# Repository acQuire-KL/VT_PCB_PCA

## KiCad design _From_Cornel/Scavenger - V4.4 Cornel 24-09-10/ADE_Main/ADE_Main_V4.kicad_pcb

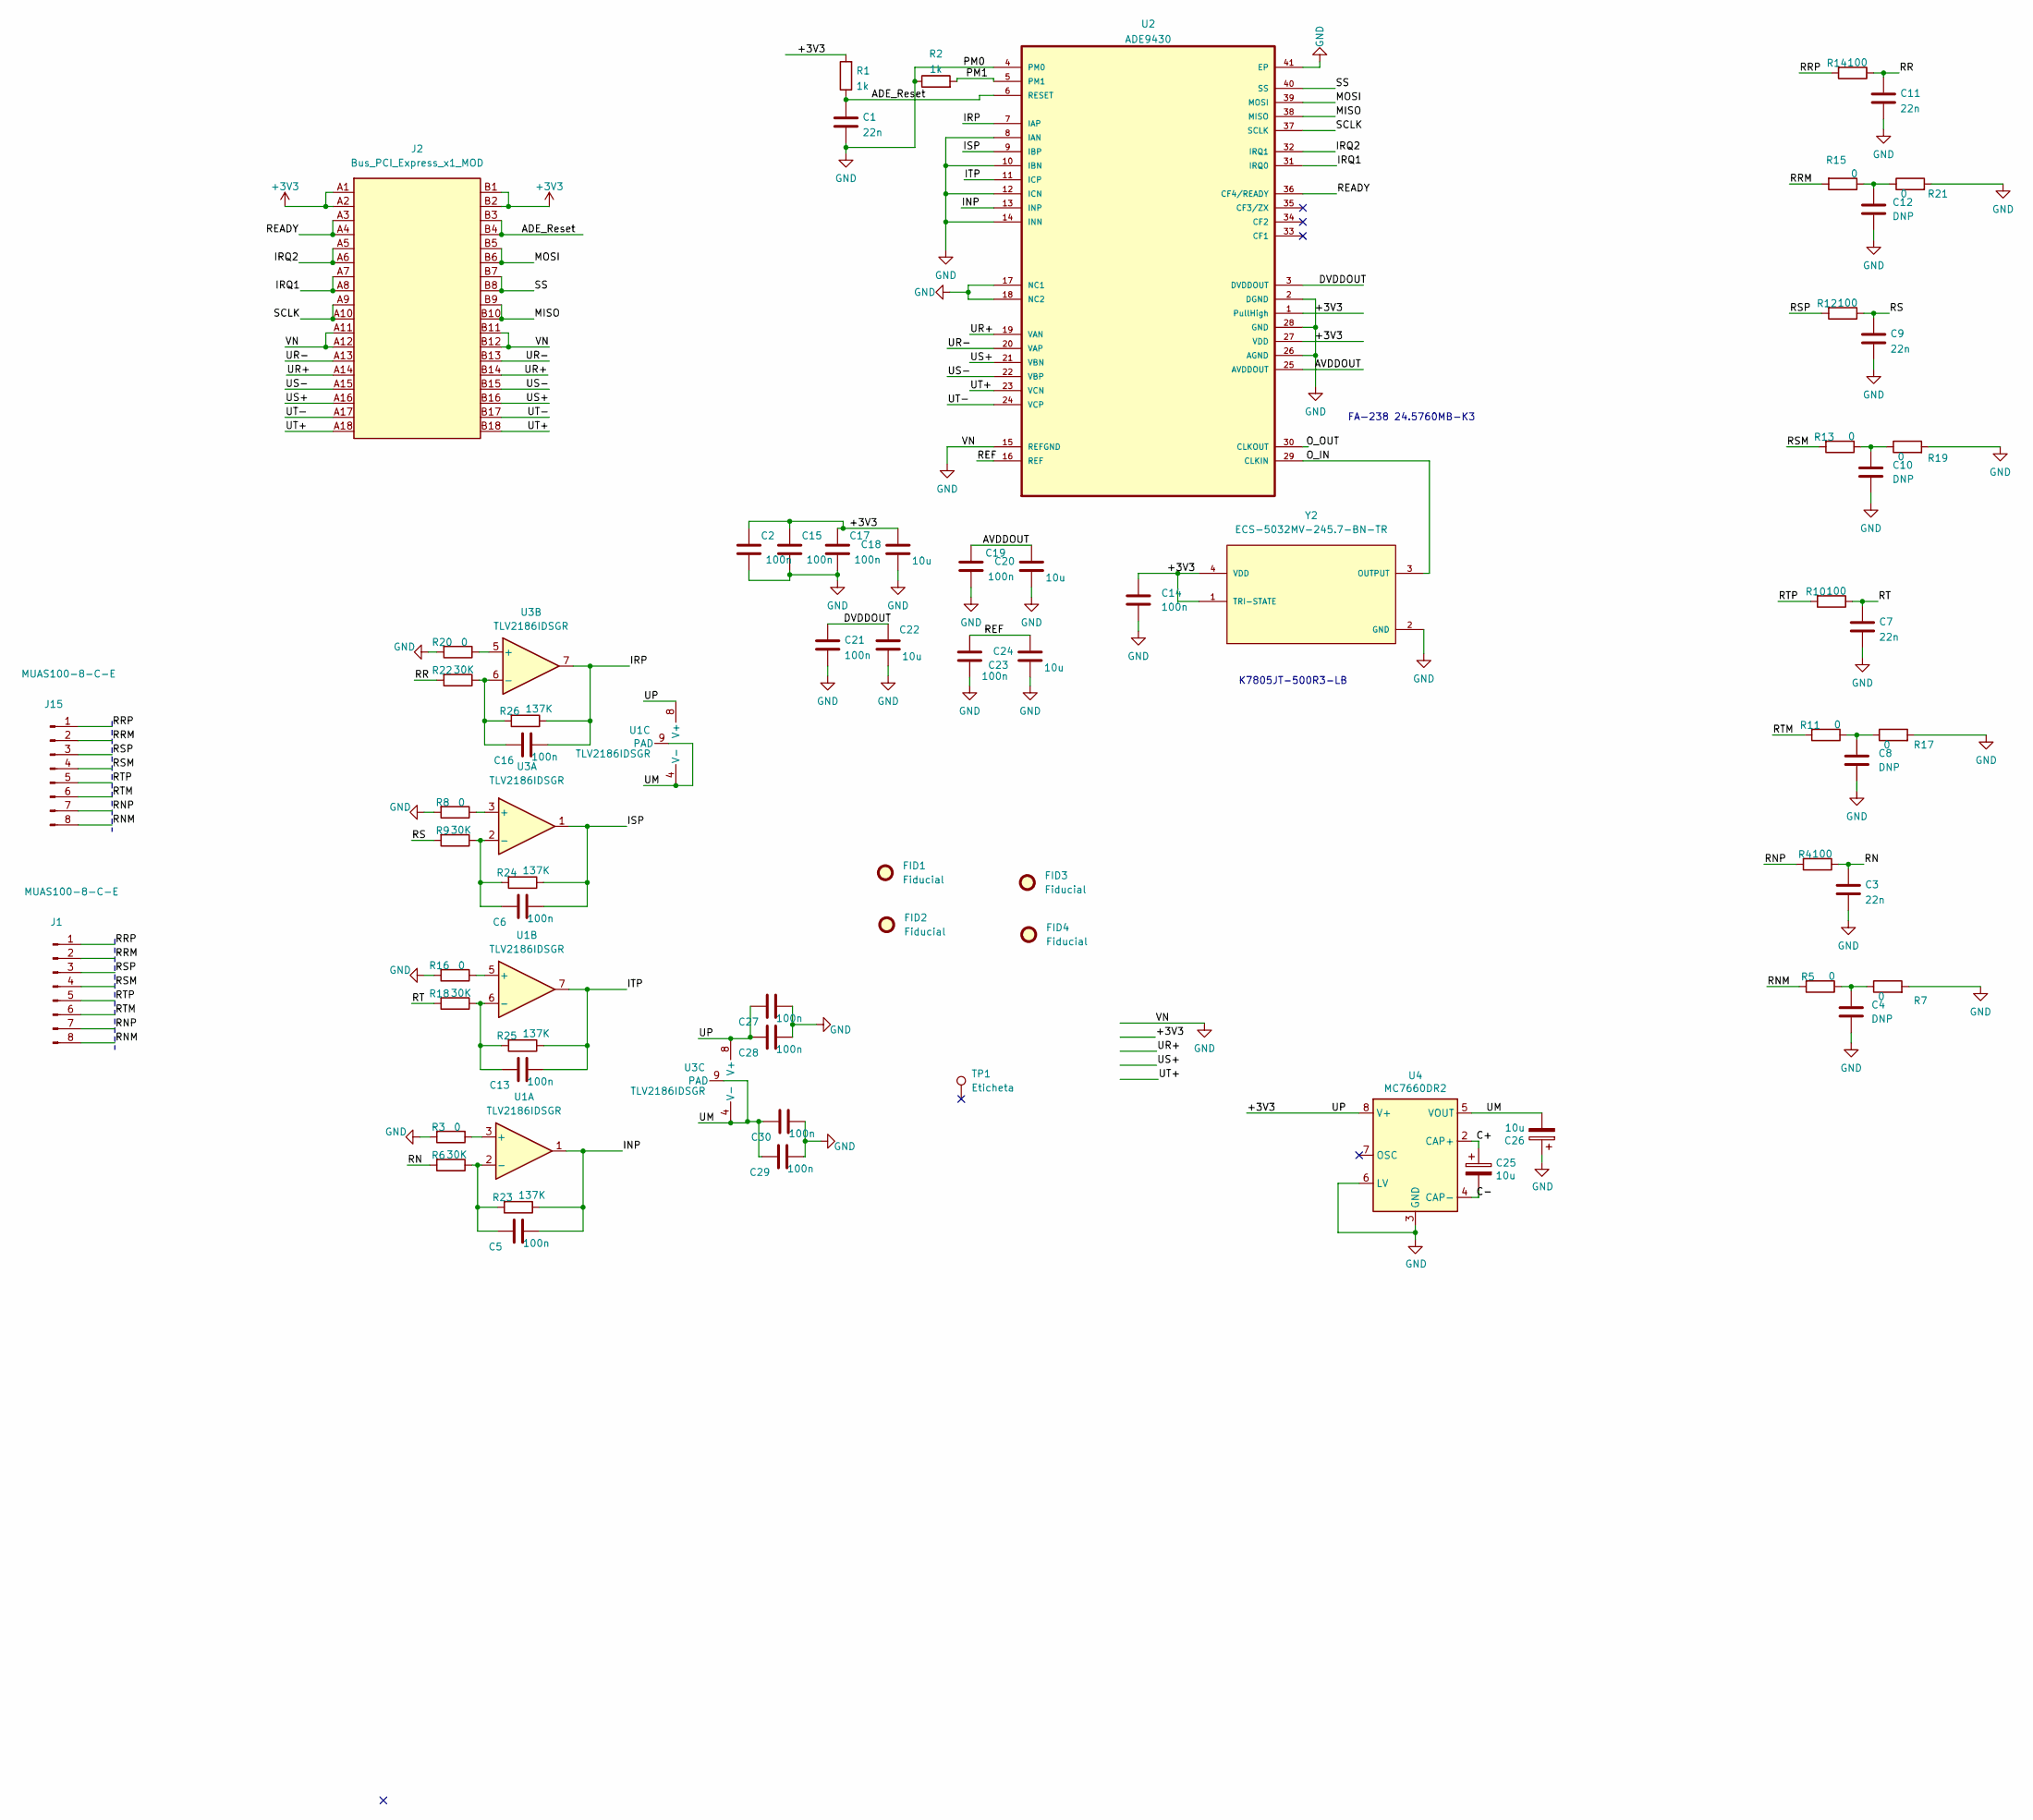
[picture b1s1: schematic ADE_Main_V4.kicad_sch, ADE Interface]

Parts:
C1, C3, C7, C9, C11: 22n; C_0402_1005Metric
C2: 100n; C_0603_1608Metric
C4, C8, C10, C12: DNP; C_0402_1005Metric
C5, C6, C13, C14, C15, C16, C17, C19, C21, C23, C27, C28, C29, C30: 100n; C_0402_1005Metric
C18, C20, C22, C24, C25, C26: 10u; C_1206_3216Metric
FID1, FID2, FID3, FID4: Fiducial; Fiducial_1mm_Mask2mm
J1: MUAS100-8-C-E; A2501-SR08-XH8AWB
J2: Bus_PCI_Express_x1_MOD; BUS_PCIexpress_x1
J15: MUAS100-8-C-E; PinHeader_1x08_P2.54mm_Vertical
R1, R2: 1k; R_0402_1005Metric
R3, R5, R7, R8, R11, R13, R15, R16, R17, R19, R20, R21: 0; R_0402_1005Metric
R4, R10, R12, R14: 100; R_0402_1005Metric
R6, R9, R18, R22: 30K; R_0402_1005Metric
R23, R24, R25, R26: 137K; R_0402_1005Metric
TP1: Eticheta
U1, U3: TLV2186IDSGR; WSON-8-1EP_2x2mm_P0.5mm_EP0.9x1.6mm_ThermalVias
U2: ADE9430; MPN AD9115BCPZ
U4: MC7660DR2; SO-8_3.9x4.9mm_P1.27mm
Y2: ECS-5032MV-245.7-BN-TR; OSC_ECS-5032MV-245.7-BN-TR

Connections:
+3V3: C2.1, C14.1, C15.1, C17.1, C18.1, C27.2, C28.2, J2.A1, J2.A2, J2.B1, J2.B2, R1.2, U1.8 (V+), U2.1 (PullHigh), U2.27 (VDD), U3.8 (V+), U4.8 (V+), Y2.1 (TRI-STATE), Y2.4 (VDD)
/ADE_Reset: C1.1, J2.B3, J2.B4, R1.1, U2.6 (RESET)
/AVDDOUT: C19.1, C20.1, U2.25 (AVDDOUT)
/C+: C25.1, U4.2 (CAP+)
/C-: C25.2, U4.4 (CAP-)
/DVDDOUT: C21.1, C22.1, U2.3 (DVDDOUT)
/INP: C5.1, R23.1, U1.1, U2.13 (INP)
/IRP: C16.1, R26.1, U2.7 (IAP), U3.7
/IRQ1: J2.A7, J2.A8, U2.31 (IRQ0)
/IRQ2: J2.A5, J2.A6, U2.32 (IRQ1)
/ISP: C6.1, R24.1, U2.9 (IBP), U3.1
/ITP: C13.1, R25.1, U1.7, U2.11 (ICP)
/MISO: J2.B9, J2.B10, U2.38 (MISO)
/MOSI: J2.B5, J2.B6, U2.39 (MOSI)
/O_IN: U2.29 (CLKIN), Y2.3 (OUTPUT)
/O_OUT: U2.30 (CLKOUT)
/PM1: R2.2, U2.5 (PM1)
/READY: J2.A3, J2.A4, U2.36 (CF4/READY)
/REF: C23.1, C24.1, U2.16 (REF)
/RN: C3.1, R4.1, R6.2
/RNM: J1.8, J15.8, R5.2
/RNP: J1.7, J15.7, R4.2
/RR: C11.1, R14.1, R22.2
/RRM: J1.2, J15.2, R15.2
/RRP: J1.1, J15.1, R14.2
/RS: C9.1, R9.2, R12.1
/RSM: J1.4, J15.4, R13.2
/RSP: J1.3, J15.3, R12.2
/RT: C7.1, R10.1, R18.2
/RTM: J1.6, J15.6, R11.2
/RTP: J1.5, J15.5, R10.2
/SCLK: J2.A9, J2.A10, U2.37 (SCLK)
/SS: J2.B7, J2.B8, U2.40 (SS)
/UM: C26.2, C29.2, C30.2, U1.4 (V-), U1.9 (PAD), U3.4 (V-), U3.9 (PAD), U4.5 (VOUT)
/UR+: J2.A14, J2.B14, U2.19 (VAN)
/UR-: J2.A13, J2.B13, U2.20 (VAP)
/US+: J2.A16, J2.B16, U2.21 (VBN)
/US-: J2.A15, J2.B15, U2.22 (VBP)
/UT+: J2.A18, J2.B18, U2.23 (VCN)
/UT-: J2.A17, J2.B17, U2.24 (VCP)
GND: C1.2, C2.2, C3.2, C4.2, C7.2, C8.2, C9.2, C10.2, C11.2, C12.2, C14.2, C15.2, C17.2, C18.2, C19.2, C20.2, C21.2, C22.2, C23.2, C24.2, C26.1, C27.1, C28.1, C29.1, C30.1, J2.A11, J2.A12, J2.B11, J2.B12, R2.1, R3.2, R7.2, R8.2, R16.2, R17.2, R19.2, R20.2, R21.2, U2.2 (DGND), U2.4 (PM0), U2.8 (IAN), U2.10 (IBN), U2.12 (ICN), U2.14 (INN), U2.15 (REFGND), U2.17 (NC1), U2.18 (NC2), U2.26 (AGND), U2.28 (GND), U2.41 (EP), U4.3 (GND), U4.6 (LV), Y2.2 (GND)
unnamed: C4.1, R5.1, R7.1
unnamed: C5.2, R6.1, R23.2, U1.2 (-)
unnamed: C6.2, R9.1, R24.2, U3.2 (-)
unnamed: C8.1, R11.1, R17.1
unnamed: C10.1, R13.1, R19.1
unnamed: C12.1, R15.1, R21.1
unnamed: C13.2, R18.1, R25.2, U1.6 (-)
unnamed: C16.2, R22.1, R26.2, U3.6 (-)
unnamed: R3.1, U1.3 (+)
unnamed: R8.1, U3.3 (+)
unnamed: R16.1, U1.5 (+)
unnamed: R20.1, U3.5 (+)

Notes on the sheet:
FA-238 24.5760MB-K3
K7805JT-500R3-LB

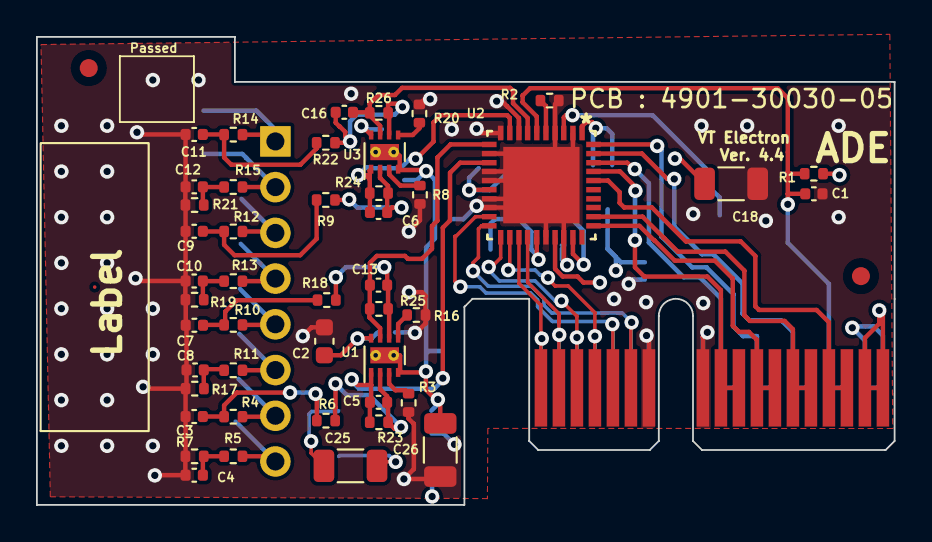
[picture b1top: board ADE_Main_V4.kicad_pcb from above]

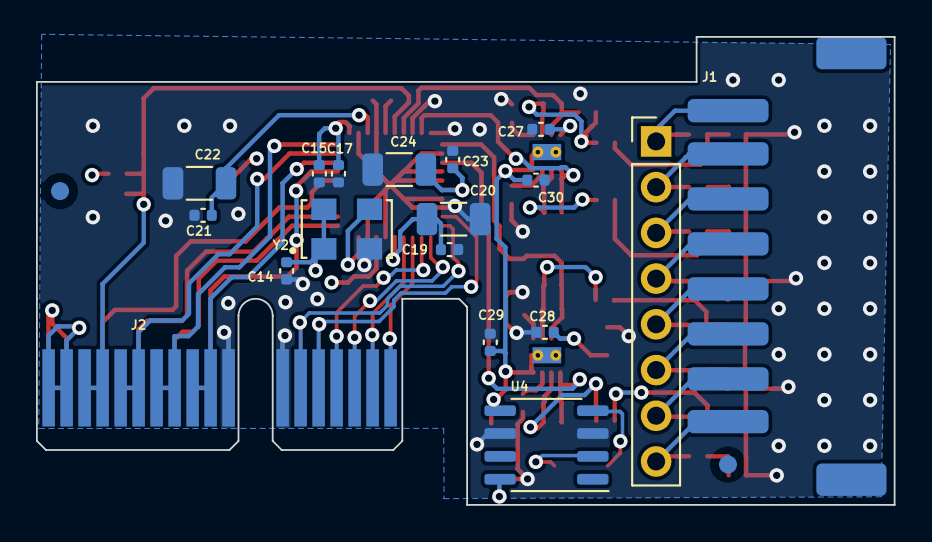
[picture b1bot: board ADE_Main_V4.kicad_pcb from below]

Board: 4 copper layers, 47.6 x 26.0 mm, 69 parts (20 on the bottom side), 52 nets.

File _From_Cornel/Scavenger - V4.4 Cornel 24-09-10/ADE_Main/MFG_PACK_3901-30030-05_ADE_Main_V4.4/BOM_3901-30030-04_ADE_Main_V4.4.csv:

"VTPN","Reference","Value","Datasheet","Footprint","Qty","DNP"
"4104-00020-00","C1,C3,C7,C9,C11","22n","~","Capacitor_SMD:C_0402_1005Metric","5",""
"4112-00100-00","C18,C20,C22,C24,C25,C26","10u","~","Capacitor_SMD:C_1206_3216Metric","6",""
"-- mixed values --","C2,C5,C6,C13,C14,C15,C16,C17,C19,C21,C23,C27,C28,C29,C30","100n","~","-- mixed values --","15",""
"4104-00000-00","C4,C8,C10,C12","DNP","~","Capacitor_SMD:C_0402_1005Metric","4",""
"","FID1,FID2,FID3,FID4","Fiducial","~","Fiducial:Fiducial_1mm_Mask2mm","4",""
"","J2","Bus_PCI_Express_x1_MOD","http://www.ritrontek.com/uploadfile/2016/1026/20161026105231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","Connector_PCBEdge:BUS_PCIexpress_x1","1",""
"4408-00010-00","J1,J15","MUAS100-8-C-E","~","-- mixed values --","2",""
"4004-00010-00","R1,R2","1k","~","Resistor_SMD:R_0402_1005Metric","2",""
"4004-02000-00","R23,R24,R25,R26","137K","~","Resistor_SMD:R_0402_1005Metric","4",""
"4004-00001-00","R3,R5,R7,R8,R11,R13,R15,R16,R17,R19,R20,R21","0","~","Resistor_SMD:R_0402_1005Metric","12",""
"4004-00020-00","R4,R10,R12,R14","100","~","Resistor_SMD:R_0402_1005Metric","4",""
"4004-00100-00","R6,R9,R18,R22","30K","~","Resistor_SMD:R_0402_1005Metric","4",""
"","TP1","Eticheta","~","Symbol:Eticheta","1",""
"4706-00030-00","U2","ADE9430","","Package_QFP:ADE9430","1",""
"4520-00030-00","U4","MC7660DR2","http://www.ti.com/lit/ds/symlink/lmc7660.pdf","Package_SO:SO-8_3.9x4.9mm_P1.27mm","1",""
"4708-00010-00","U1,U3","TLV2186IDSGR","-- mixed values --","Package_SON:WSON-8-1EP_2x2mm_P0.5mm_EP0.9x1.6mm_ThermalVias","2",""
"4712-00020-00","Y2","ECS-5032MV-245.7-BN-TR","","Oscillator:OSC_ECS-5032MV-245.7-BN-TR","1",""

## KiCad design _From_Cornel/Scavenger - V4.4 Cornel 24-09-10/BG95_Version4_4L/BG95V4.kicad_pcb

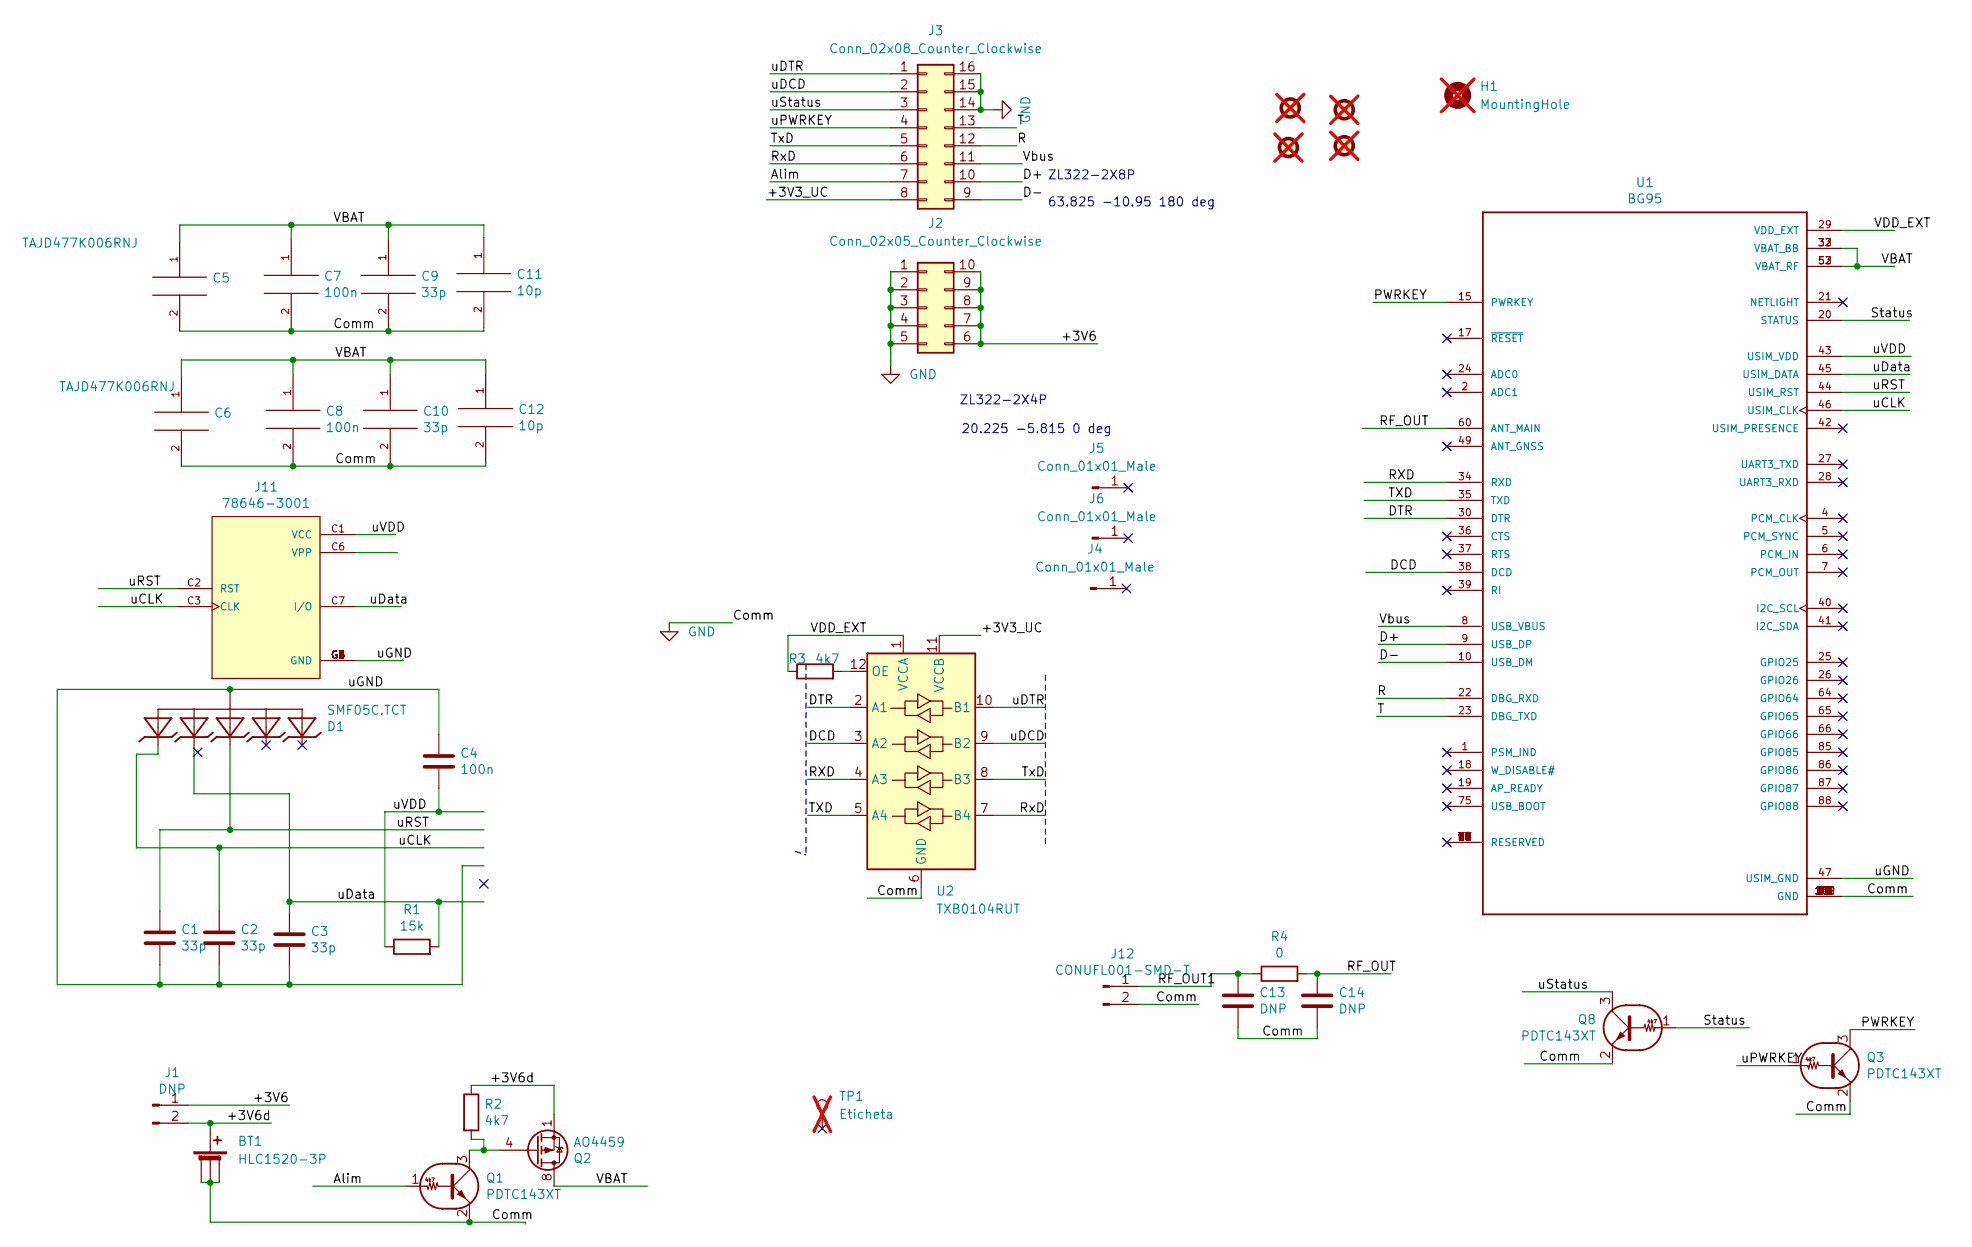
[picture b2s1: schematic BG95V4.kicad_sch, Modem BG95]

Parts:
BT1: HLC1520-3P
C1, C2, C3: 33p; C_0603_1608Metric
C4: 100n; C_0603_1608Metric
C5, C6: TAJD477K006RNJ; CP_EIA-7361-38_AVX-V_Pad2.18x3.30mm_HandSolder
C7, C8: 100n; C_0603_1608Metric_Pad1.05x0.95mm_HandSolder
C9, C10: 33p; C_0603_1608Metric_Pad1.05x0.95mm_HandSolder
C11, C12: 10p; C_0603_1608Metric_Pad1.05x0.95mm_HandSolder
C13, C14: DNP; C_0603_1608Metric
D1: SMF05C.TCT; SC70-6
FID1, FID2, FID3, FID4: Fiducial; Fiducial_1mm_Mask2mm; not fitted
H1: MountingHole; MountingHole_2.5mm Simpla; not fitted
J1: DNP; PinHeader_1x02_P2.54mm_Vertical
J2: Conn_02x05_Counter_Clockwise; PinHeader_2x05_P2.54mm_Vertical_SMD_MOD
J3: Conn_02x08_Counter_Clockwise; PinHeader_2x08_P2.54mm_Vertical_SMD_MOD
J4, J5, J6: Conn_01x01_Male; TestPoint_Pad_5.1x5.1mm
J11: 78646-3001; MOLEX_78646-3001; DIGI-KEY_PART_NUMBER WM9364CT-ND
J12: CONUFL001-SMD-T; U.FL_Molex_MCRF_73412-0110_Vertical
Q1, Q3, Q8: PDTC143XT; SOT-23
Q2: AO4459; SOIC-8_3.9x4.9mm_P1.27mm
R1: 15k; R_0603_1608Metric
R2, R3: 4k7; R_0603_1608Metric
R4: 0; R_0603_1608Metric
TP1: Eticheta; not fitted
U1: BG95; XCVR_BG95M3LA-64-SGNS
U2: TXB0104RUT; Texas_R_PUQFN-N12

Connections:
/+3V3_UC: J3.8, U2.11 (VCCB)
/+3V6: J1.1, J2.6, J2.7, J2.8, J2.9, J2.10
/+3V6d: BT1.1 (+), J1.2, Q2.1 (S), Q2.2 (S), Q2.3 (S), R2.1
/Alim: J3.7, Q1.1 (B)
/D+: J3.10, U1.9 (USB_DP)
/D-: J3.9, U1.10 (USB_DM)
/DCD: U1.38 (DCD), U2.3 (A2)
/DTR: U1.30 (DTR), U2.2 (A1)
/PWRKEY: Q3.3 (C), U1.15 (PWRKEY)
/R: J3.12, U1.22 (DBG_RXD)
/RF_OUT: C14.1, R4.2, U1.60 (ANT_MAIN)
/RF_OUT1: C13.1, J12.1, R4.1
/RXD: U1.34 (RXD), U2.4 (A3)
/RxD: J3.6, U2.7 (B4)
/Status: Q8.1 (B), U1.20 (STATUS)
/T: J3.13, U1.23 (DBG_TXD)
/TXD: U1.35 (TXD), U2.5 (A4)
/TxD: J3.5, U2.8 (B3)
/VBAT: C5.1, C6.1, C7.1, C8.1, C9.1, C10.1, C11.1, C12.1, Q2.5 (D), Q2.6 (D), Q2.7 (D), Q2.8 (D), U1.32 (VBAT_BB), U1.33 (VBAT_BB), U1.52 (VBAT_RF), U1.53 (VBAT_RF)
/VDD_EXT: R3.1, U1.29 (VDD_EXT), U2.1 (VCCA)
/Vbus: J3.11, U1.8 (USB_VBUS)
/uCLK: C2.1, D1.6, J11.C3 (CLK), U1.46 (USIM_CLK)
/uDCD: J3.2, U2.9 (B2)
/uDTR: J3.1, U2.10 (B1)
/uData: C3.1, D1.5, J11.C7 (I/O), R1.2, U1.45 (USIM_DATA)
/uGND: C1.2, C2.2, C3.2, C4.1, D1.2, J11.C5 (GND), J11.G1 (GND), J11.G2 (GND), J11.G3 (GND), J11.G4 (GND), J11.G5 (GND), J11.G6 (GND), U1.47 (USIM_GND)
/uPWRKEY: J3.4, Q3.1 (B)
/uRST: C1.1, D1.4, J11.C2 (RST), U1.44 (USIM_RST)
/uStatus: J3.3, Q8.3 (C)
/uVDD: C4.2, J11.C1 (VCC), R1.1, U1.43 (USIM_VDD)
GND: BT1.2 (-), BT1.3 (-), BT1.4 (-), C5.2, C6.2, C7.2, C8.2, C9.2, C10.2, C11.2, C12.2, C13.2, C14.2, J2.1, J2.2, J2.3, J2.4, J2.5, J3.14, J3.15, J3.16, J12.2, Q1.2 (E), Q3.2 (E), Q8.2 (E), U1.3 (GND), U1.31 (GND), U1.48 (GND), U1.50 (GND), U1.54 (GND), U1.55 (GND), U1.58 (GND), U1.59 (GND), U1.61 (GND), U1.62 (GND), U1.67 (GND), U1.68 (GND), U1.69 (GND), U1.70 (GND), U1.71 (GND), U1.72 (GND), U1.73 (GND), U1.74 (GND), U1.79 (GND), U1.80 (GND), U1.81 (GND), U1.82 (GND), U1.89 (GND), U1.90 (GND), U1.91 (GND), U1.100 (GND), U1.101 (GND), U1.102 (GND), U2.6 (GND)
unnamed: Q1.3 (C), Q2.4 (G), R2.2
unnamed: R3.2, U2.12 (OE)

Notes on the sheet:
ZL322-2X8P
20.225 -5.815 0 deg
ZL322-2X4P
63.825 -10.95 180 deg

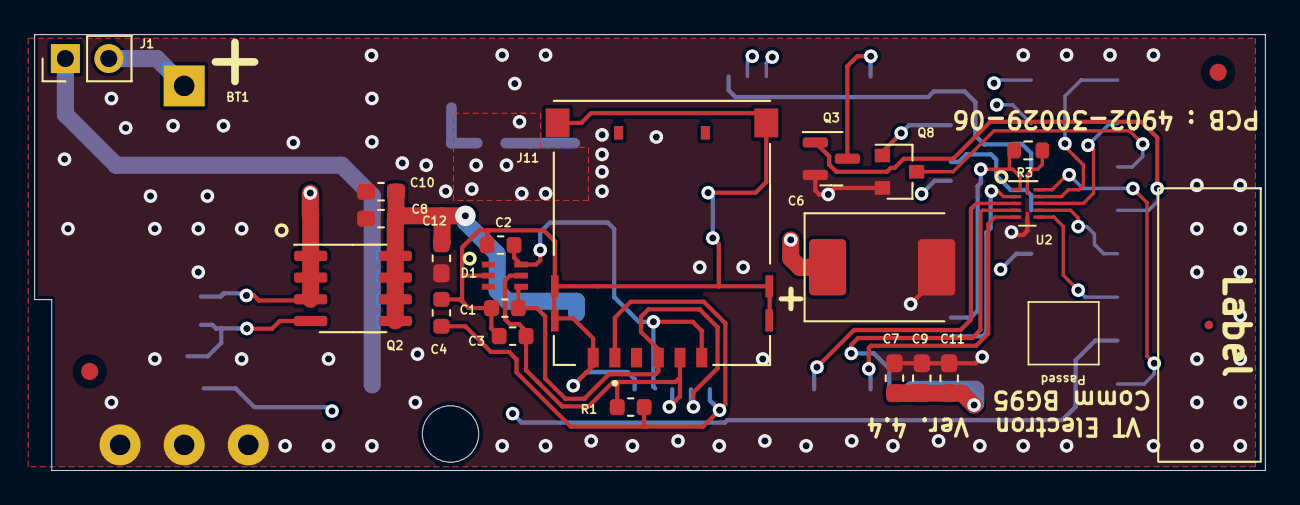
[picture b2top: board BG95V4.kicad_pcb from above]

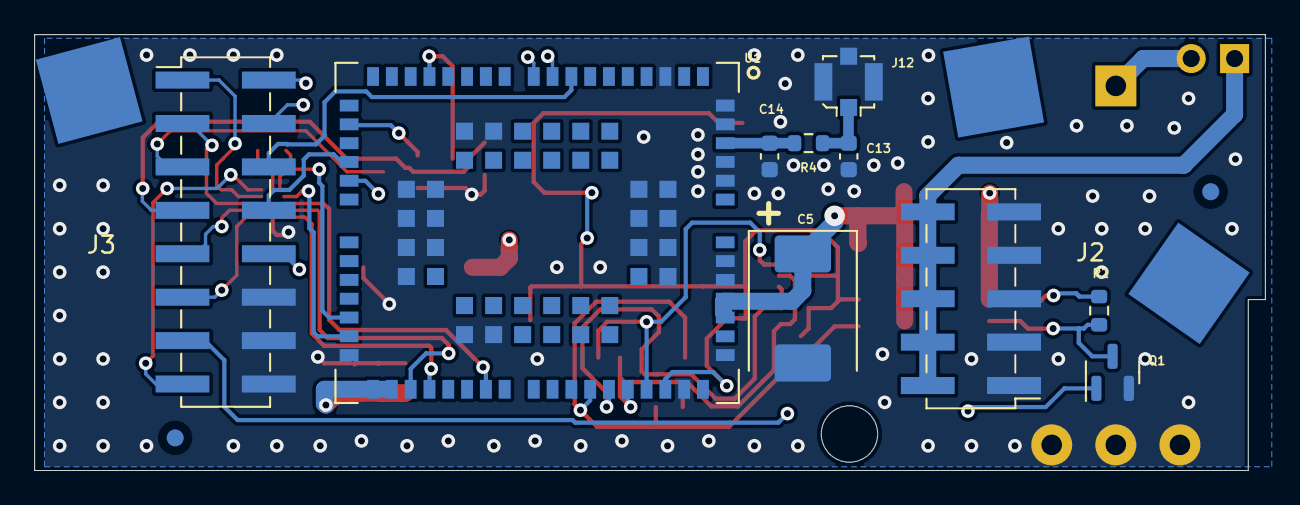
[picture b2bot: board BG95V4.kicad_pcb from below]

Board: 4 copper layers, 72.0 x 25.5 mm, 40 parts (15 on the bottom side), 33 nets.

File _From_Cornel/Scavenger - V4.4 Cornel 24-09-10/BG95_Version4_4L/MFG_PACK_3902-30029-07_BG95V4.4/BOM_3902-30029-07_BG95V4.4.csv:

"VTPN","Reference","Value","Datasheet","Footprint","Qty","DNP"
"4200-00020-00","BT1","HLC1520-3P","~","Battery:HLC1520-3P","1",""
"4106-00040-00","C1,C2,C3,C9,C10","33p","~","-- mixed values --","5",""
"4106-00020-00","C4,C7,C8","100n","~","-- mixed values --","3",""
"4128-00100-00","C5,C6","TAJD477K006RNJ","~","Capacitor_Tantalum_SMD:CP_EIA-7361-38_AVX-V_Pad2.18x3.30mm_HandSolder","2",""
"4106-00010-00","C11,C12","10p","~","Capacitor_SMD:C_0603_1608Metric_Pad1.05x0.95mm_HandSolder","2",""
"-- mixed values --","C13,C14,J1","DNP","~","-- mixed values --","3",""
"4724-00010-00","D1","SMF05C.TCT","","Diode_SMD:SC70-6","1",""
"","FID1,FID2,FID3,FID4","Fiducial","~","Fiducial:Fiducial_1mm_Mask2mm","4","DNP"
"","H1","MountingHole","~","MountingHole:MountingHole_2.5mm  Simpla","1","DNP"
"4402-00020-00","J2","Conn_02x05_Counter_Clockwise","~","Connector_PinHeader_2.54mm:PinHeader_2x05_P2.54mm_Vertical_SMD_MOD","1",""
"4402-00030-00","J3","Conn_02x08_Counter_Clockwise","~","Connector_PinHeader_2.54mm:PinHeader_2x08_P2.54mm_Vertical_SMD_MOD","1",""
"4753-00010-00","J4,J5,J6","Conn_01x01_Male","~","TestPoint:TestPoint_Pad_5.1x5.1mm","3",""
"4414-00020-00","J11","78646-3001","","Connector_Molex:MOLEX_78646-3001","1",""
"4416-00010-00","J12","CONUFL001-SMD-T","~","Connector_Coaxial:U.FL_Molex_MCRF_73412-0110_Vertical","1",""
"4500-00010-00","Q1,Q3,Q8","PDTC143XT","","Package_TO_SOT_SMD:SOT-23","3",""
"4530-00010-00","Q2","AO4459","https://www.onsemi.com/pub/Collateral/FDS9435A-D.PDF","Package_SO:SOIC-8_3.9x4.9mm_P1.27mm","1",""
"4006-00160-00","R1","15k","~","Resistor_SMD:R_0603_1608Metric","1",""
"4006-00150-00","R2,R3","4k7","~","Resistor_SMD:R_0603_1608Metric","2",""
"4006-00001-00","R4","0","~","Resistor_SMD:R_0603_1608Metric","1",""
"","TP1","Eticheta","~","Symbol:Eticheta","1","DNP"
"4716-00010-00","U1","BG95","1.1","BG95:XCVR_BG95M3LA-64-SGNS","1",""
"4702-00010-00","U2","TXB0104RUT","http://www.ti.com/lit/ds/symlink/txb0104.pdf","Package_DFN_QFN:Texas_R_PUQFN-N12","1",""

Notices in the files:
parts and their libraries:
Copyright 2021 Accelerated Designs. All rights reserved.
